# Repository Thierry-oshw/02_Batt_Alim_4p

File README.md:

# 02_Batt_Alim_4p

Module Batt_alim avec 4 pins.

Le module Batt_Alim permet de gérer la charge d'une batterie Lipo constituée d'une seule cellule (4.2V) à partir d'une source de type 5V USB.
Il permet aussi de récupérer cette tension batterie variable et de reconstituer un 5V constant grâce à un DCDC.

[La licence est celle du CERN Open Hardware Licence version 2; CERN-OHL-P ; permissive.](https://github.com/Thierry-oshw/02_Batt_Alim_4p/blob/main/LICENSE.txt)

## Schéma et fonctionnement

Ci-joint le schéma de la version de 2021_02_23 // Here schematic of version 2021_02_23:

Le module fonctionne de la façon suivante:
Il faut l'alimenter avec une tension 5V +-5% (typiquement celle de l'USB classique) sur la pin Vext. (Ne pas oublier GND bien sûr).

Il faut brancher la batterie Lipo sur V_bat+ et GND. La batterie Lipo doit être constituée d'une seule cellule, qui doit être chargée à 4.2V, présente une tension de 3.7V typique, et dont la tension de mise en protection est de 3V. La résistance R7 de 10kOhms permet de régler la puce TP4056 sur un courant de charge de 130mA. La batterie Lipo doit donc avoir une capacité d'au moins 2*130mAh, soit 260mAh au minimum. Plus d'information sur [www.tp4056.com](www.tp4056.com).

La sortie 5V est une tension issue du DCDC.

La LED D6 indique la présence de 5V à la sortie du DCDC, avec "5V ON" comme étiquette.

Les LEDs D2 et D3 indiquent respectivement la charge et le mode standby du TP4056. Les étiquettes sont "CHG" et "STBY".

## Fonctionnalités
- Petit (28x25.2 mm)
- Faible coût (2 couches avec composants d'un seul côté)
- Connecteur avec pas de 2.54 mm + empreinte crénelée pour connexion carte à carte

## Outils utilisés

- [Kicad V6](https://www.kicad.org/)

## Fabrication du circuit

Ce circuit a été testé de fond en comble sur de nombreux projets

## Contributeurs

- Thierry Orlandi ([Hardware Freelance](https://www.linkedin.com/in/thierry-orlandi))
- Yohann Belair ([R&D Freelance](https://github.com/ciborg971))

## Licence
[CERN Open Hardware Licence Version 2](https://github.com/Thierry-oshw/02_Batt_Alim_4p/blob/main/LICENSE.txt)

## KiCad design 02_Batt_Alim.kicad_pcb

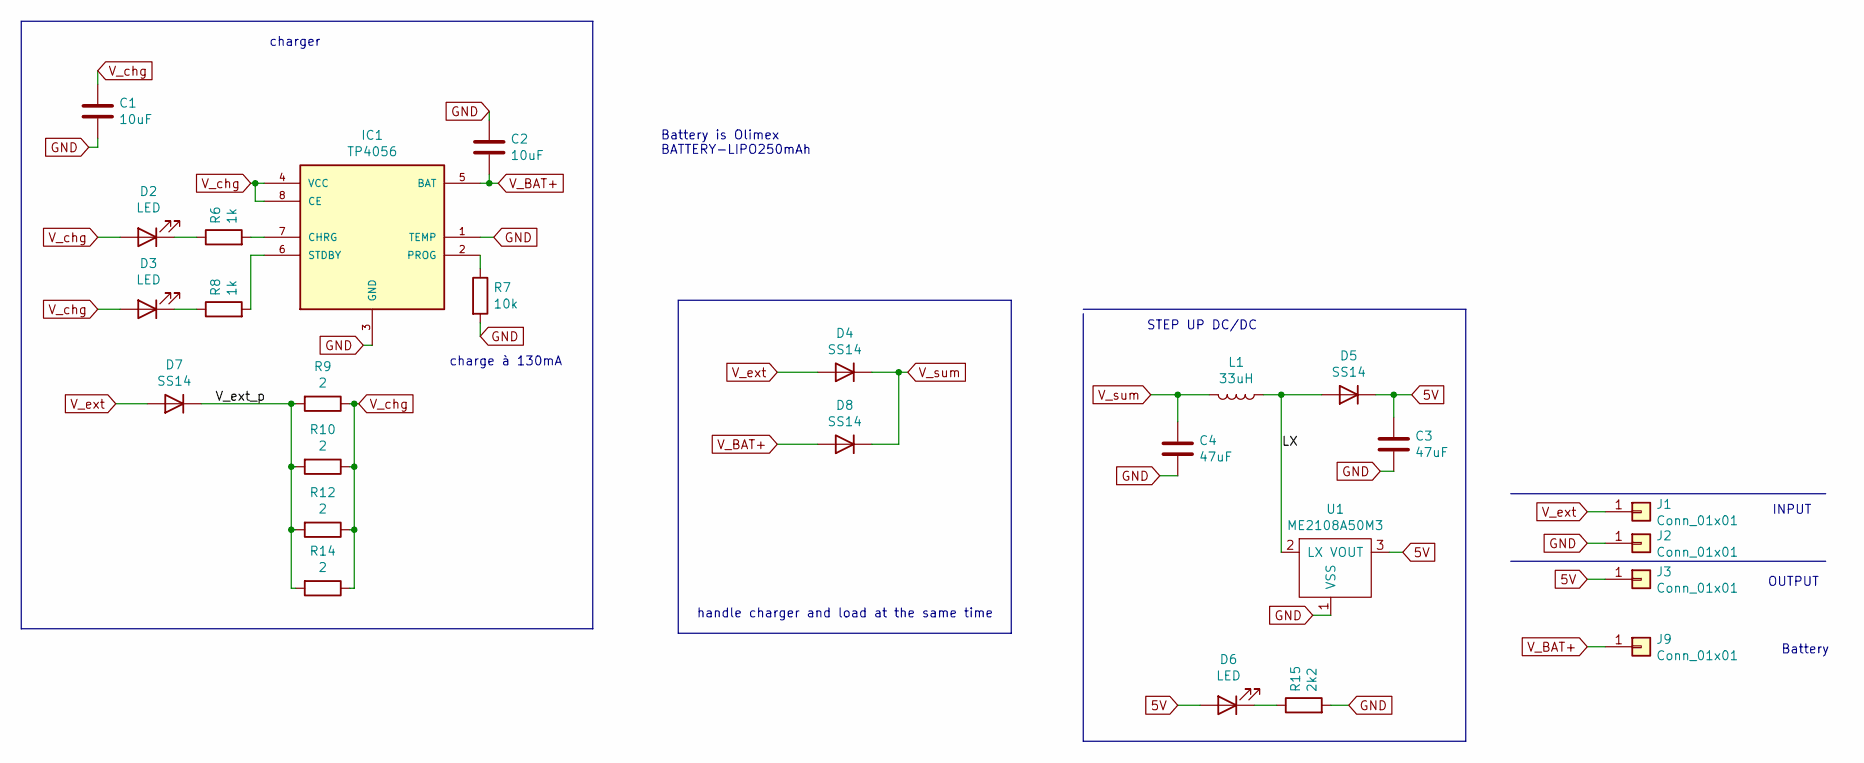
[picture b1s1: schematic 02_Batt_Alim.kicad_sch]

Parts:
C1, C2: 10uF; C_0603_1608Metric; LCSC C19702
C3, C4: 47uF; C_1210_3225Metric; LCSC C77101
D2, D3, D6: LED; D_0603_1608Metric; LCSC C2286
D4, D5, D7, D8: SS14; D_SMA; LCSC C2480
IC1: TP4056; SOP-8; LCSC C16581
J1, J2, J3, J9: Conn_01x01; Castellated_conn
L1: 33uH; L_10.4x10.4_H4.8; LCSC C9936
R6, R8: 1k; R_0603_1608Metric; LCSC C21190
R7: 10k; R_0603_1608Metric; LCSC C22765
R9, R10, R12, R14: 2; R_0603_1608Metric; LCSC C22977
R15: 2k2; R_0603_1608Metric; LCSC C4190
U1: ME2108A50M3; SOT-23_Handsoldering; LCSC C14839

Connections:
5V: C3.1, D5.1 (K), D6.2 (A), J3.1, U1.3 (VOUT)
/LX: D5.2 (A), L1.1, U1.2 (LX)
/V_ext_p: D7.1 (K), R9.2, R10.2, R12.2, R14.2
GND: C1.2, C2.1, C3.2, C4.2, IC1.1 (TEMP), IC1.3 (GND), J2.1, R7.2, R15.2, U1.1 (VSS)
unnamed: D2.1 (K), R6.1
unnamed: D3.1 (K), R8.1
unnamed: D6.1 (K), R15.1
unnamed: IC1.2 (PROG), R7.1
unnamed: IC1.6 (STDBY), R8.2
unnamed: IC1.7 (CHRG), R6.2
V_BAT+: C2.2, D8.2 (A), IC1.5 (BAT), J9.1
V_chg: C1.1, D2.2 (A), D3.2 (A), IC1.4 (VCC), IC1.8 (CE), R9.1, R10.1, R12.1, R14.1
V_ext: D4.2 (A), D7.2 (A), J1.1
V_sum: C4.1, D4.1 (K), D8.1 (K), L1.2

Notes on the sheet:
handle charger and load at the same time
STEP UP DC/DC
INPUT
charger
Battery
Battery is Olimex BATTERY-LIPO250mAh
OUTPUT
charge à 130mA

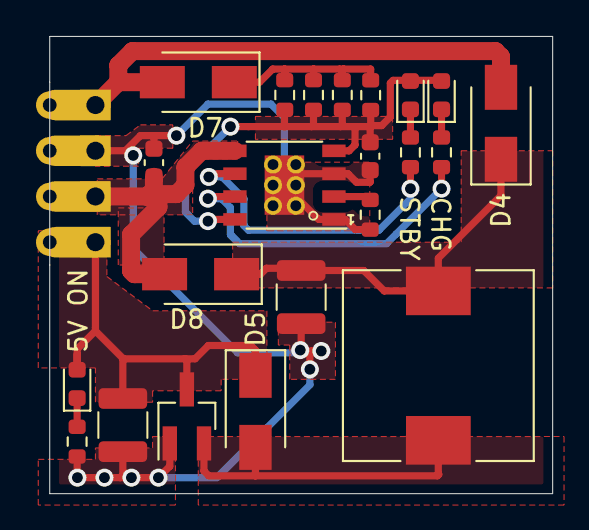
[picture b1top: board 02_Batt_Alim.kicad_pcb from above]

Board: 2 copper layers, 27.9 x 25.4 mm, 26 parts (0 on the bottom side), 14 nets.

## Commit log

2021-09-14 initialisation
    from 02_Batt_alim project at tag 2021_03_03_fab
2021-09-14 maj librairies
    split librairies avec maj chemin, symboles et empreintes + pcb
2021-11-28 maj readme
    ajout schema.png pour plus de clarté
2023-05-02 chgt nom fichier licence
2023-05-10 maj kicad v6
2023-05-10 maj schéma avec champ lcsc
2023-05-10 pcb passage kicad v6
2023-05-10 maj schema retouche placement et routage fabrication
2023-05-10 bom + placement
2023-05-28 maj readme
2023-05-28 maj readme : changement lien license
